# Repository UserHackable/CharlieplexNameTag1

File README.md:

## CharlieplexNameTag 

### Board dimensions

* (393701, 196850) original units
* (3.9370, 1.9685) inches
* (100.0001, 49.9999) mm

| Front | Back |
| --- | --- |
|  |  |

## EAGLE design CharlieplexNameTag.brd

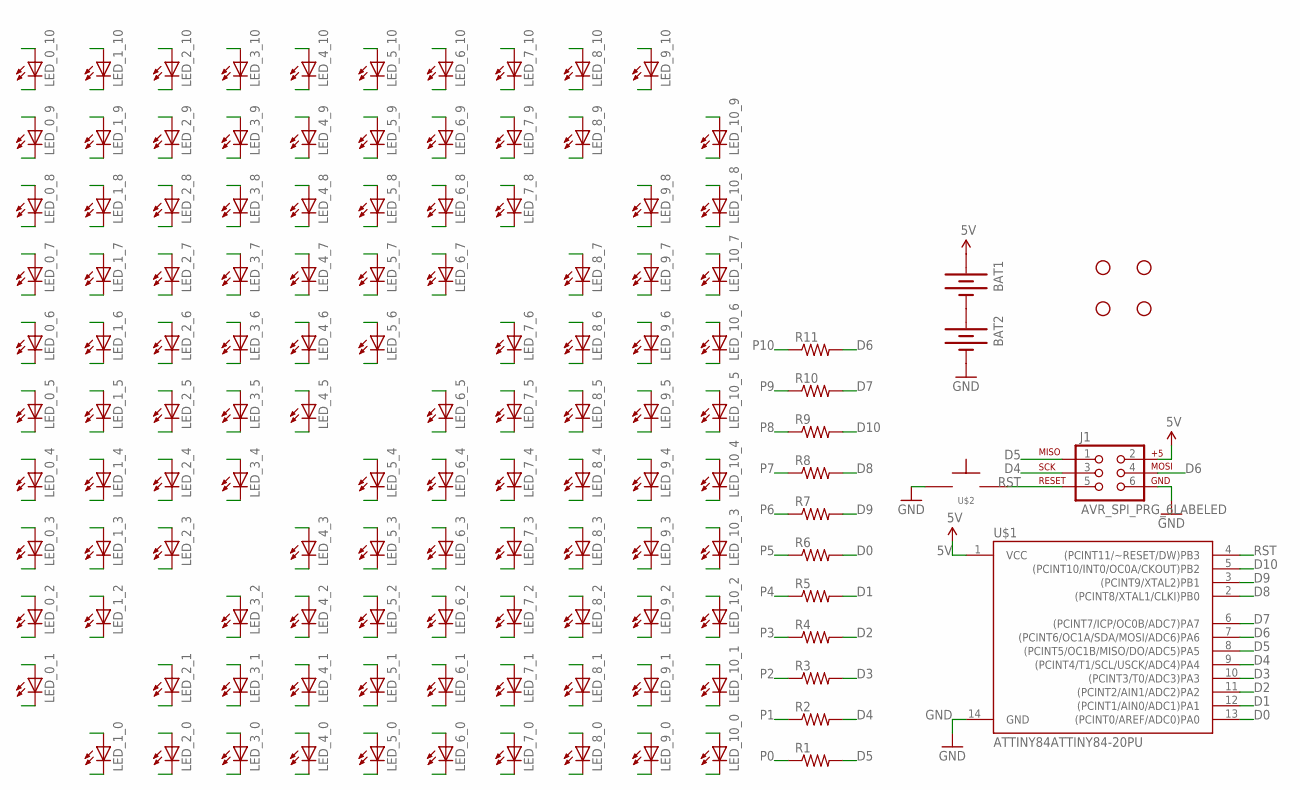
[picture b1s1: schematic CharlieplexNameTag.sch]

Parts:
BAT1, BAT2: BATTERYAAA; BATTERY-AAA
J1: AVR_SPI_PRG_6LABELED; 2X3-NS
LED_0_1, LED_0_2, LED_0_3, LED_0_4, LED_0_5, LED_0_6, LED_0_7, LED_0_8, LED_0_9, LED_0_10, LED_1_0, LED_1_2, LED_1_3, LED_1_4, LED_1_5, LED_1_6, LED_1_7, LED_1_8, LED_1_9, LED_1_10, LED_2_0, LED_2_1, LED_2_3, LED_2_4, LED_2_5, LED_2_6, LED_2_7, LED_2_8, LED_2_9, LED_2_10, LED_3_0, LED_3_1, LED_3_2, LED_3_4, LED_3_5, LED_3_6, LED_3_7, LED_3_8, LED_3_9, LED_3_10, LED_4_0, LED_4_1, LED_4_2, LED_4_3, LED_4_5, LED_4_6, LED_4_7, LED_4_8, LED_4_9, LED_4_10, LED_5_0, LED_5_1, LED_5_2, LED_5_3, LED_5_4, LED_5_6, LED_5_7, LED_5_8, LED_5_9, LED_5_10, LED_6_0, LED_6_1, LED_6_2, LED_6_3, LED_6_4, LED_6_5, LED_6_7, LED_6_8, LED_6_9, LED_6_10, LED_7_0, LED_7_1, LED_7_2, LED_7_3, LED_7_4, LED_7_5, LED_7_6, LED_7_8, LED_7_9, LED_7_10, LED_8_0, LED_8_1, LED_8_2, LED_8_3, LED_8_4, LED_8_5, LED_8_6, LED_8_7, LED_8_9, LED_8_10, LED_9_0, LED_9_1, LED_9_2, LED_9_3, LED_9_4, LED_9_5, LED_9_6, LED_9_7, LED_9_8, LED_9_10, LED_10_0, LED_10_1, LED_10_2, LED_10_3, LED_10_4, LED_10_5, LED_10_6, LED_10_7, LED_10_8, LED_10_9: LED3MM
R1, R2, R3, R4, R5, R6, R7, R8, R9, R10, R11: RESISTORAXIAL-0.3; AXIAL-0.3
STANDOFF1, STANDOFF2, STANDOFF3, STANDOFF4: STAND-OFF
U$1: ATTINY84ATTINY84-20PU; DIL14
U$2: TAC_SPST_NO

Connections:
5V: BAT1.PWR@1 (+), J1.2, U$1.1 (VCC)
D0: R6.P$2 (2), U$1.13 ((PCINT0/AREF/ADC0)PA0)
D1: R5.P$2 (2), U$1.12 ((PCINT1/AIN0/ADC1)PA1)
D2: R4.P$2 (2), U$1.11 ((PCINT2/AIN1/ADC2)PA2)
D3: R3.P$2 (2), U$1.10 ((PCINT3/T0/ADC3)PA3)
D4: J1.3, R2.P$2 (2), U$1.9 ((PCINT4/T1/SCL/USCK/ADC4)PA4)
D5: J1.1, R1.P$2 (2), U$1.8 ((PCINT5/OC1B/MISO/DO/ADC5)PA5)
D6: J1.4, R11.P$2 (2), U$1.7 ((PCINT6/OC1A/SDA/MOSI/ADC6)PA6)
D7: R10.P$2 (2), U$1.6 ((PCINT7/ICP/OC0B/ADC7)PA7)
D8: R8.P$2 (2), U$1.2 ((PCINT8/XTAL1/CLKI)PB0)
D9: R7.P$2 (2), U$1.3 ((PCINT9/XTAL2)PB1)
D10: R9.P$2 (2), U$1.5 ((PCINT10/INT0/OC0A/CKOUT)PB2)
GND: BAT2.GND@1 (-), J1.6, U$1.14 (GND), U$2.P$1
unnamed: BAT1.GND@1 (-), BAT2.PWR@1 (+)
P0: LED_0_1.K (C), LED_0_2.K (C), LED_0_3.K (C), LED_0_4.K (C), LED_0_5.K (C), LED_0_6.K (C), LED_0_7.K (C), LED_0_8.K (C), LED_0_9.K (C), LED_0_10.K (C), LED_1_0.A, LED_2_0.A, LED_3_0.A, LED_4_0.A, LED_5_0.A, LED_6_0.A, LED_7_0.A, LED_8_0.A, LED_9_0.A, LED_10_0.A, R1.P$1 (1)
P1: LED_0_1.A, LED_1_0.K (C), LED_1_2.K (C), LED_1_3.K (C), LED_1_4.K (C), LED_1_5.K (C), LED_1_6.K (C), LED_1_7.K (C), LED_1_8.K (C), LED_1_9.K (C), LED_1_10.K (C), LED_2_1.A, LED_3_1.A, LED_4_1.A, LED_5_1.A, LED_6_1.A, LED_7_1.A, LED_8_1.A, LED_9_1.A, LED_10_1.A, R2.P$1 (1)
P2: LED_0_2.A, LED_1_2.A, LED_2_0.K (C), LED_2_1.K (C), LED_2_3.K (C), LED_2_4.K (C), LED_2_5.K (C), LED_2_6.K (C), LED_2_7.K (C), LED_2_8.K (C), LED_2_9.K (C), LED_2_10.K (C), LED_3_2.A, LED_4_2.A, LED_5_2.A, LED_6_2.A, LED_7_2.A, LED_8_2.A, LED_9_2.A, LED_10_2.A, R3.P$1 (1)
P3: LED_0_3.A, LED_1_3.A, LED_2_3.A, LED_3_0.K (C), LED_3_1.K (C), LED_3_2.K (C), LED_3_4.K (C), LED_3_5.K (C), LED_3_6.K (C), LED_3_7.K (C), LED_3_8.K (C), LED_3_9.K (C), LED_3_10.K (C), LED_4_3.A, LED_5_3.A, LED_6_3.A, LED_7_3.A, LED_8_3.A, LED_9_3.A, LED_10_3.A, R4.P$1 (1)
P4: LED_0_4.A, LED_1_4.A, LED_2_4.A, LED_3_4.A, LED_4_0.K (C), LED_4_1.K (C), LED_4_2.K (C), LED_4_3.K (C), LED_4_5.K (C), LED_4_6.K (C), LED_4_7.K (C), LED_4_8.K (C), LED_4_9.K (C), LED_4_10.K (C), LED_5_4.A, LED_6_4.A, LED_7_4.A, LED_8_4.A, LED_9_4.A, LED_10_4.A, R5.P$1 (1)
P5: LED_0_5.A, LED_1_5.A, LED_2_5.A, LED_3_5.A, LED_4_5.A, LED_5_0.K (C), LED_5_1.K (C), LED_5_2.K (C), LED_5_3.K (C), LED_5_4.K (C), LED_5_6.K (C), LED_5_7.K (C), LED_5_8.K (C), LED_5_9.K (C), LED_5_10.K (C), LED_6_5.A, LED_7_5.A, LED_8_5.A, LED_9_5.A, LED_10_5.A, R6.P$1 (1)
P6: LED_0_6.A, LED_1_6.A, LED_2_6.A, LED_3_6.A, LED_4_6.A, LED_5_6.A, LED_6_0.K (C), LED_6_1.K (C), LED_6_2.K (C), LED_6_3.K (C), LED_6_4.K (C), LED_6_5.K (C), LED_6_7.K (C), LED_6_8.K (C), LED_6_9.K (C), LED_6_10.K (C), LED_7_6.A, LED_8_6.A, LED_9_6.A, LED_10_6.A, R7.P$1 (1)
P7: LED_0_7.A, LED_1_7.A, LED_2_7.A, LED_3_7.A, LED_4_7.A, LED_5_7.A, LED_6_7.A, LED_7_0.K (C), LED_7_1.K (C), LED_7_2.K (C), LED_7_3.K (C), LED_7_4.K (C), LED_7_5.K (C), LED_7_6.K (C), LED_7_8.K (C), LED_7_9.K (C), LED_7_10.K (C), LED_8_7.A, LED_9_7.A, LED_10_7.A, R8.P$1 (1)
P8: LED_0_8.A, LED_1_8.A, LED_2_8.A, LED_3_8.A, LED_4_8.A, LED_5_8.A, LED_6_8.A, LED_7_8.A, LED_8_0.K (C), LED_8_1.K (C), LED_8_2.K (C), LED_8_3.K (C), LED_8_4.K (C), LED_8_5.K (C), LED_8_6.K (C), LED_8_7.K (C), LED_8_9.K (C), LED_8_10.K (C), LED_9_8.A, LED_10_8.A, R9.P$1 (1)
P9: LED_0_9.A, LED_1_9.A, LED_2_9.A, LED_3_9.A, LED_4_9.A, LED_5_9.A, LED_6_9.A, LED_7_9.A, LED_8_9.A, LED_9_0.K (C), LED_9_1.K (C), LED_9_2.K (C), LED_9_3.K (C), LED_9_4.K (C), LED_9_5.K (C), LED_9_6.K (C), LED_9_7.K (C), LED_9_8.K (C), LED_9_10.K (C), LED_10_9.A, R10.P$1 (1)
P10: LED_0_10.A, LED_1_10.A, LED_2_10.A, LED_3_10.A, LED_4_10.A, LED_5_10.A, LED_6_10.A, LED_7_10.A, LED_8_10.A, LED_9_10.A, LED_10_0.K (C), LED_10_1.K (C), LED_10_2.K (C), LED_10_3.K (C), LED_10_4.K (C), LED_10_5.K (C), LED_10_6.K (C), LED_10_7.K (C), LED_10_8.K (C), LED_10_9.K (C), R11.P$1 (1)
RST: J1.5, U$1.4 ((PCINT11/~RESET/DW)PB3), U$2.P$2

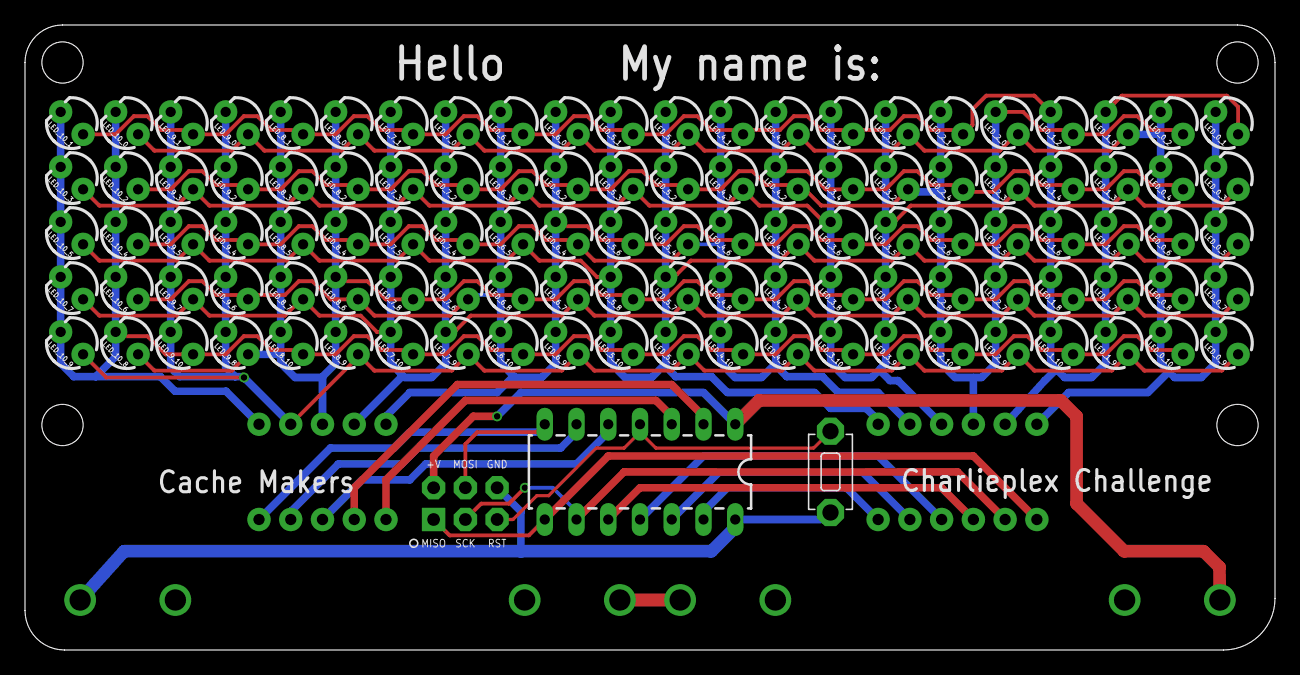
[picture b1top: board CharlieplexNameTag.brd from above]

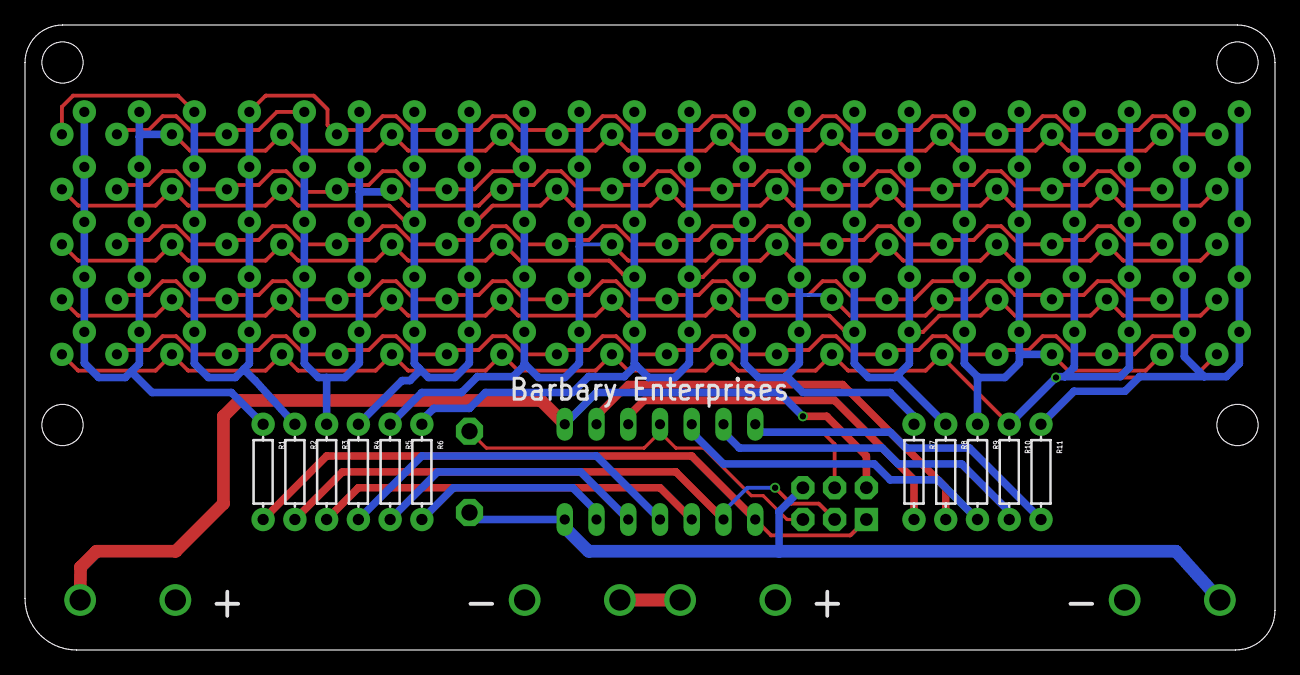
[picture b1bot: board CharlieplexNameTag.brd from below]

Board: 2 copper layers, 100.0 x 50.0 mm, 130 parts (13 on the bottom side), 26 nets.

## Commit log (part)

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2016-04-08 from Makefile

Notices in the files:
parts and their libraries:
SparkFun-DigitalIC: Licensing: Creative Commons ShareAlike 4.0 International - https://creativecommons.org/licenses/by-sa/4.0
